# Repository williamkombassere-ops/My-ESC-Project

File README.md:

# My-ESC-Project 🚀

Contrôleur de vitesse électronique (ESC) open-source pour moteur brushless triphasé, conçu sur mesure avec KiCad et piloté par un microcontrôleur STM32.

---

## 📌 Aperçu du projet

Ce projet consiste en la conception complète (schématique, routage PCB et logique de commande) d'un ESC (Electronic Speed Controller) adapté aux moteurs synchrones triphasés (BLDC). Il est dimensionné pour supporter des courants forts et implémente une commutation adaptée au pilotage de moteurs de forte puissance.

---

## ⚙️ Spécifications techniques

* **Microcontrôleur :** STM32
* **Type de moteur :** Moteur brushless triphasé (BLDC)
* **Contrôle de vitesse :** Régulation par PWM (rapport cyclique variable)
* **Commutation :** Commutation 120° via STM32 + Drivers de MOSFET IR2101
* **Étage de puissance :** 6 MOSFETs N-Channel
* **Conception PCB :** Pistes de **1.5 mm** optimisées pour le passage de courants forts
* **Outil de conception :** KiCad 9.0

---

## 📂 Structure du dépôt

```text
My-ESC-Project/
├── Images/                               # Captures et schémas visuels du projet
├── Electronic Speed Controller.kicad_sch # Schématique électronique (KiCad)
├── Electronic Speed Controller.kicad_pcb # Routage du circuit imprimé (KiCad)
├── Electronic Speed Controller.kicad_pro # Fichier projet KiCad
└── README.md                             # Documentation du projet

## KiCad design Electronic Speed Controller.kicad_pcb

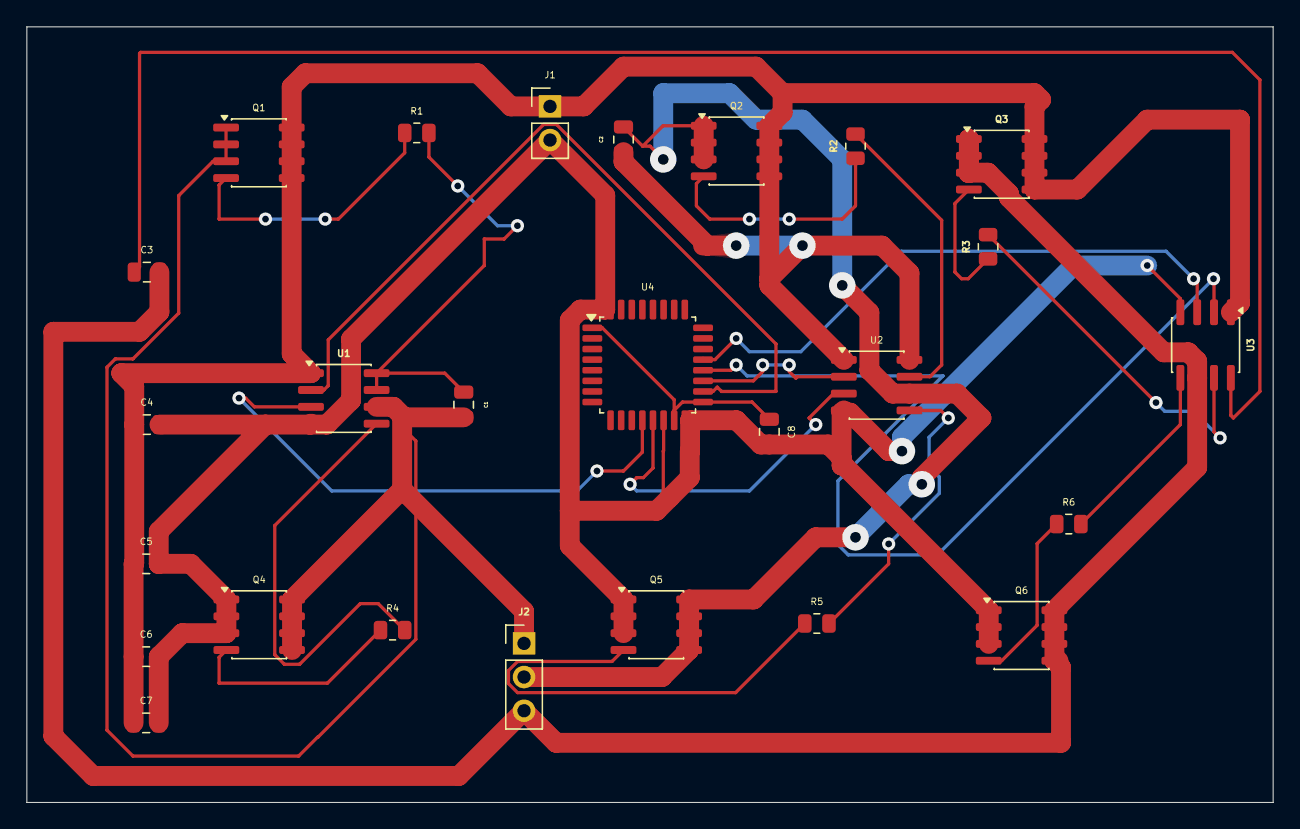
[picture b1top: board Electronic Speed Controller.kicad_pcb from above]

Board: 2 copper layers, 94.0 x 58.5 mm, 26 parts (0 on the bottom side), 25 nets.

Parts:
C1, C2, C3, C8: 100; C_0805_2012Metric
C4, C5, C6, C7: 480; C_0805_2012Metric
J1: Conn_01x02_Pin; PinHeader_1x02_P2.54mm_Vertical
J2: Conn_01x03_Pin; PinHeader_1x03_P2.54mm_Vertical
Q1, Q2, Q3, Q4, Q5, Q6: IRF7403; SOIC-8_3.9x4.9mm_P1.27mm
R1, R2, R3, R4, R5, R6: 22; R_0805_2012Metric
U1, U2, U3: IR2101; SOIC-8_3.9x4.9mm_P1.27mm
U4: STM32G431KBTx; LQFP-32_7x7mm_P0.8mm

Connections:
+3.3V: C8.1, U4.1 (VDD), U4.15 (VDDA), U4.17 (VDD)
/PWM_H_A: U1.2 (HIN), U4.18 (PA8)
/PWM_H_B: U2.2 (HIN), U4.19 (PA9)
/PWM_H_C: U3.2 (HIN), U4.20 (PA10)
/PWM_L_A: U1.3 (LIN), U4.12 (PA7)
/PWM_L_B: U2.3 (LIN), U4.13 (PB0)
/PWM_L_C: U3.3 (LIN), U4.21 (PA11)
GND: C4.2, C5.2, C6.2, C7.2, C8.2, J1.2, Q4.1 (S), Q4.2 (S), Q4.3 (S), Q5.1 (S), Q5.2 (S), Q5.3 (S), Q6.1 (S), Q6.2 (S), Q6.3 (S), U1.4 (COM), U2.4 (COM), U3.4 (COM), U4.14 (VSSA), U4.16 (VSS), U4.32 (VSS)
unnamed: C1.2, J2.1, Q1.1 (S), Q1.2 (S), Q1.3 (S), Q4.5 (D), Q4.6 (D), Q4.7 (D), Q4.8 (D), U1.6 (VS)
unnamed: C2.2, J2.2, Q2.1 (S), Q2.2 (S), Q2.3 (S), Q5.5 (D), Q5.6 (D), Q5.7 (D), Q5.8 (D), U2.6 (VS)
unnamed: C3.2, J2.3, Q3.1 (S), Q3.2 (S), Q3.3 (S), Q6.5 (D), Q6.6 (D), Q6.7 (D), Q6.8 (D), U3.6 (VS)
unnamed: Q1.4 (G), R1.1
unnamed: Q2.4 (G), R2.1
unnamed: Q3.4 (G), R3.1
unnamed: Q4.4 (G), R4.1
unnamed: Q5.4 (G), R5.1
unnamed: Q6.4 (G), R6.1
unnamed: C1.1, R1.2, U1.7 (HO), U1.8 (VB)
unnamed: R4.2, U1.5 (LO)
unnamed: R2.2, U2.7 (HO)
unnamed: R5.2, U2.5 (LO)
unnamed: C2.1, C4.1, C5.1, C6.1, C7.1, J1.1, Q1.5 (D), Q1.6 (D), Q1.7 (D), Q1.8 (D), Q2.5 (D), Q2.6 (D), Q2.7 (D), Q2.8 (D), Q3.5 (D), Q3.6 (D), Q3.7 (D), Q3.8 (D), U1.1 (VCC), U2.1 (VCC), U2.8 (VB), U3.1 (VCC)
unnamed: R3.2, U3.7 (HO)
unnamed: R6.2, U3.5 (LO)
unnamed: C3.1, U3.8 (VB)

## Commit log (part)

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2026-04-05 Initial commit - Projet ESC complet
    Schéma, PCB et fichiers de projet KiCad 9.0
